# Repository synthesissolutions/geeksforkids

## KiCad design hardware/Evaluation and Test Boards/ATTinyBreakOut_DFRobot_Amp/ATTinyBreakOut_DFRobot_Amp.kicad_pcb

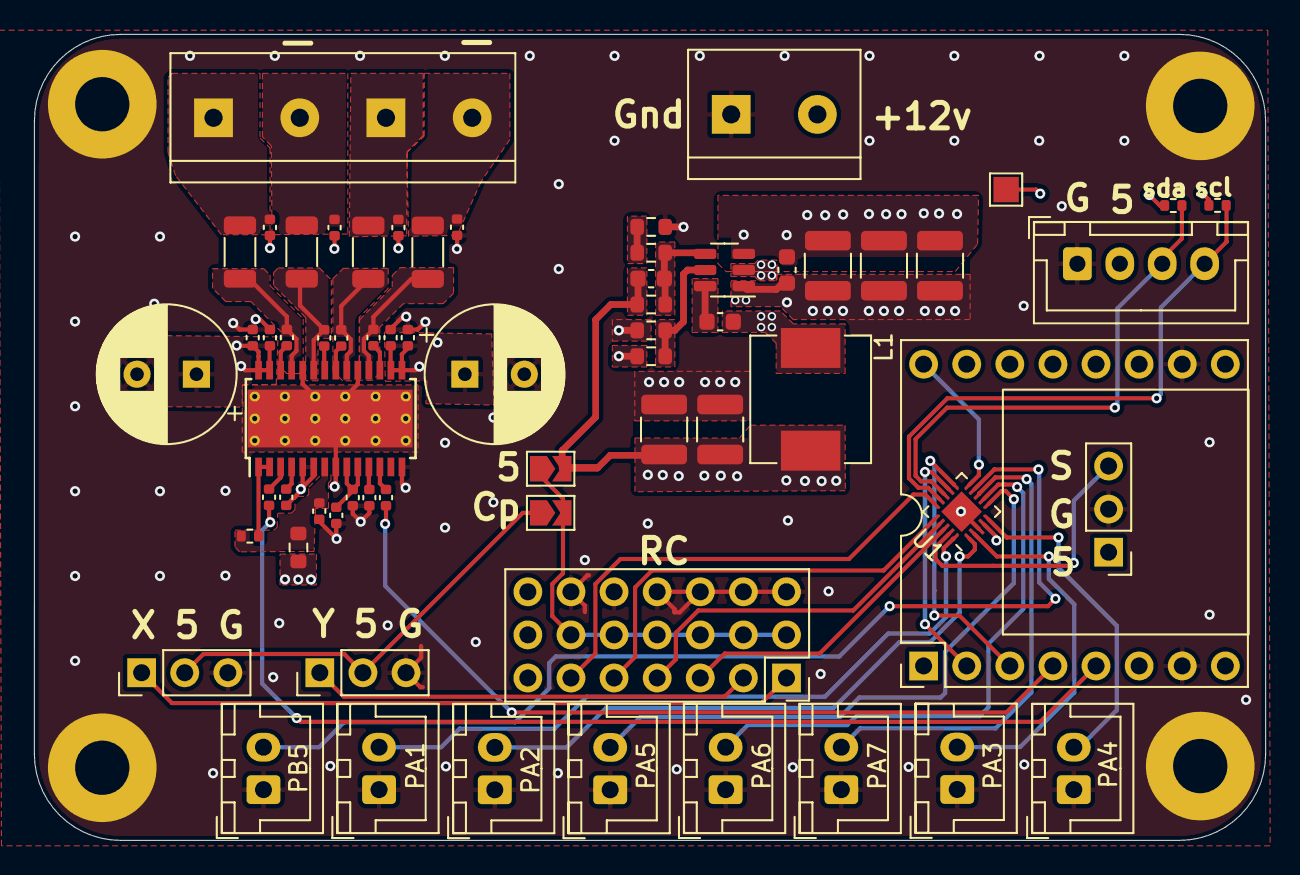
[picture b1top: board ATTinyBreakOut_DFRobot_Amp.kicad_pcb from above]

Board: 4 copper layers, 72.6 x 47.5 mm, 71 parts (0 on the bottom side), 51 nets.

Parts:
C1, C5: 100uF; CP_Radial_D8.0mm_P3.50mm
C2, C6: 100nF; C_0402_1005Metric
C3, C7, C9, C10, C24, C25: 1nF; C_0402_1005Metric
C4, C14, C15: 1uF; C_0402_1005Metric
C8, C13, C26, C29: 0.22uF; C_0402_1005Metric
C11, C12, C27, C28: 0.68uF; C_0402_1005Metric
C16, C17, C18: 10µF; C_1210_3225Metric
C19, C20: 0.1µF; C_0603_1608Metric
C21: 150pF; C_0603_1608Metric
C22, C23: 47µF; C_1210_3225Metric
FB1, FB2, FB3, FB4: 120Ohm@100MHz; L_1206_3216Metric
H1, H2, H3, H4: MountingHole; MountingHole_3.2mm_M3_Pad
J1: Right Out; TerminalBlock_bornier-2_P5.08mm
J2: Steering; PinHeader_1x03_P2.54mm_Vertical
J3: Throttle; PinHeader_1x03_P2.54mm_Vertical
J4: Main Power; TerminalBlock_bornier-2_P5.08mm
J5: RC Signal; PinSocket_1x07_P2.54mm_Vertical
J6: ATT Prog; PinHeader_1x03_P2.54mm_Vertical
J7: RC Power; PinSocket_2x07_P2.54mm_Vertical
J8: I2C; JST_XH_B4B-XH-A_1x04_P2.50mm_Vertical
J9: PA3; JST_XH_B2B-XH-A_1x02_P2.50mm_Vertical
J10: DFRobot_Mini; DFRobotMini_2x08_P2.54mm_Vertical
J11: PA7; JST_XH_B2B-XH-A_1x02_P2.50mm_Vertical
J12: PA5; JST_XH_B2B-XH-A_1x02_P2.50mm_Vertical
J13: PA1; JST_XH_B2B-XH-A_1x02_P2.50mm_Vertical
J14: PB5; JST_XH_B2B-XH-A_1x02_P2.50mm_Vertical
J15: PA2; JST_XH_B2B-XH-A_1x02_P2.50mm_Vertical
J16: Left Out; TerminalBlock_bornier-2_P5.08mm
J17: PA6; JST_XH_B2B-XH-A_1x02_P2.50mm_Vertical
J18: PA4; JST_XH_B2B-XH-A_1x02_P2.50mm_Vertical
JP1: Car Power; SolderJumper-2_P1.3mm_Open_TrianglePad1.0x1.5mm
JP2: 5v; SolderJumper-2_P1.3mm_Open_TrianglePad1.0x1.5mm
L1: 10µH; L_Sunlord_MWSA0603S
R1: 10R; R_0603_1608Metric
R2, R4: 4.7k; R_0402_1005Metric
R3: 100k; R_0402_1005Metric
R11: 511kΩ 1%; R_0603_1608Metric
R12: 105kΩ 1%; R_0603_1608Metric
R13: 100kΩ 1%; R_0603_1608Metric
R14: 13.3kΩ 1%; R_0603_1608Metric
R15: 240Ω 1%; R_0603_1608Metric
TP1: 5V; TestPoint_Pad_1.5x1.5mm
U1: ATtiny1616-M; VQFN-20-1EP_3x3mm_P0.4mm_EP1.7x1.7mm
U3: TPA3110D2; HTSSOP-28-1EP_4.4x9.7mm_P0.65mm_EP3.4x9.5mm_Mask2.4x6.17mm_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
U4: TPS54302; SOT-23-6

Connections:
+5V: C21.1, C22.1, C23.1, J6.1, J8.2, J10.1, JP2.2 (B), L1.2, R2.1, R4.1, R13.1, TP1.1, U1.4 (VCC)
+12V: C1.1, C2.1, C3.1, C5.1, C6.1, C7.1, C16.1, C17.1, C18.1, C19.1, J4.2, R1.1, R11.1, U3.15 (PVCCR), U3.16 (PVCCR), U3.27 (PVCCL), U3.28 (PVCCL), U4.3 (VIN)
+12VA: C4.1, R1.2, R3.1, U3.7 (AVCC)
/Audio_Module/AUDIO_IN_1_NL: C27.1, U3.4 (LINN)
/Audio_Module/AUDIO_IN_1_NR: C12.1, U3.11 (RINN)
/Audio_Module/AUDIO_IN_1_PL: C28.2, U3.3 (LINP)
/Audio_Module/AUDIO_IN_1_PR: C11.2, U3.12 (RINP)
/Audio_Module/AUDIO_OUT_FILT_NL: C10.2, FB2.2, J16.2
/Audio_Module/AUDIO_OUT_FILT_NR: C25.2, FB4.2, J1.2
/Audio_Module/AUDIO_OUT_FILT_PL: C9.1, FB1.2, J16.1
/Audio_Module/AUDIO_OUT_FILT_PR: C24.1, FB3.2, J1.1
/Audio_Module/GVDD: C14.1, C15.1, U3.9 (GVDD), U3.10 (PLIMIT)
/Audio_Module/~SD_2: R3.2, U3.1 (~SD), U3.2 (~FAULT)
/Buck_Converter/BOOT: C20.1, U4.6 (BOOT)
/Buck_Converter/EN: R11.2, R12.1, U4.5 (EN)
/Buck_Converter/FB: C21.2, R13.2, R14.1, U4.4 (FB)
/Buck_Converter/SW: C20.2, L1.1, U4.2 (SW)
ATT_Prog: J6.3, U1.19 (~RESET/PA0)
AUDIO_IN_PL: C28.1, J10.9
AUDIO_IN_PR: C11.1, J10.7
Car_Power: J7.1, J7.3, J7.5, J7.7, J7.9, J7.11, JP1.2 (B), JP2.1 (A)
DFR_Busy: J10.2, U1.10 (PB4)
DFR_Rx: J10.3, U1.12 (PB2)
DFR_Tx: J10.5, U1.11 (PB3)
GND: C1.2, C2.2, C3.2, C4.2, C5.2, C6.2, C7.2, C9.2, C10.1, C12.2, C14.2, C15.2, C16.2, C17.2, C18.2, C19.2, C22.2, C23.2, C24.2, C25.1, C27.2, H1.1, H2.1, H3.1, H4.1, J2.3, J3.3, J4.1, J6.2, J7.2, J7.4, J7.6, J7.8, J7.10, J7.12, J8.1, J9.1, J10.13, J10.14, J11.1, J12.1, J13.1, J14.1, J15.1, J17.1, J18.1, R12.2, R15.2, U1.3 (GND), U1.21 (GND), U3.5 (GAIN0), U3.6 (GAIN1), U3.8 (AGND), U3.14 (PBTL), U3.19 (PGND), U3.24 (PGND), U3.29 (GND), U4.1 (GND)
I2C_SCL: J8.4, R2.2, U1.14 (PB0)
I2C_SDA: J8.3, R4.2, U1.13 (PB1)
unnamed: J2.2, J3.2, JP1.1 (A)
unnamed: R14.2, R15.1
unnamed: C26.2, U3.22 (BSNL)
unnamed: C29.2, U3.21 (BSNR)
unnamed: C8.2, U3.26 (BSPL)
unnamed: C13.2, U3.17 (BSPR)
unnamed: C26.1, FB2.1, U3.23 (OUTNL)
unnamed: C29.1, FB3.1, U3.20 (OUTNR)
unnamed: C8.1, FB1.1, U3.25 (OUTPL)
unnamed: C13.1, FB4.1, U3.18 (OUTPR)
PA1: J13.2, U1.20 (PA1)
PA2: J15.2, U1.1 (PA2)
PA3: J9.2, U1.2 (PA3)
PA4: J18.2, U1.5 (PA4)
PA5: J12.2, U1.6 (PA5)
PA6: J17.2, U1.7 (PA6)
PA7: J11.2, U1.8 (PA7)
PB5: J14.2, U1.9 (PB5)
RC_3: J5.3, U1.18 (PC3)
RC_4: J5.4, U1.17 (PC2)
RC_5: J5.5, U1.16 (PC1)
RC_6: J5.6, U1.15 (PC0)
RC_X: J2.1, J5.1
RC_Y: J3.1, J5.2

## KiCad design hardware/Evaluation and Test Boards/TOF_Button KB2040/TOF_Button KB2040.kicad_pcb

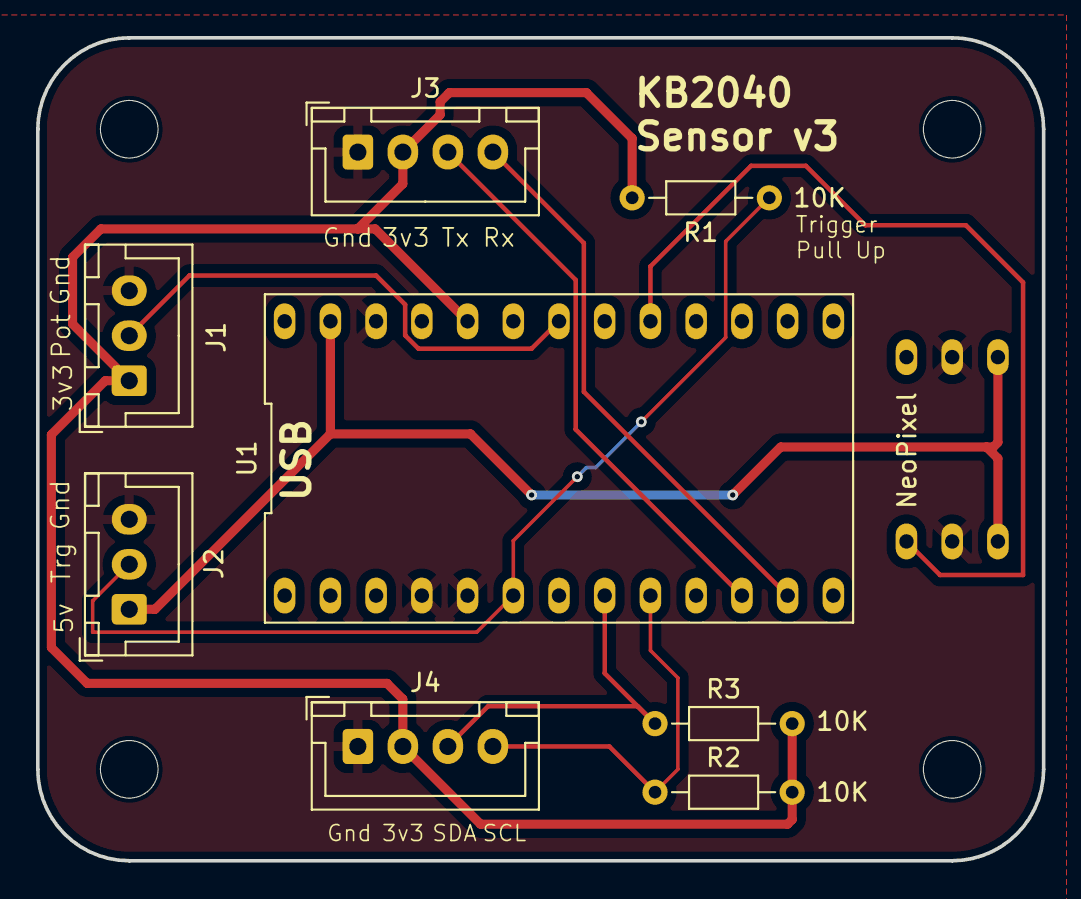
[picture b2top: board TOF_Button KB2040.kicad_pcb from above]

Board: 2 copper layers, 55.9 x 45.7 mm, 13 parts (1 on the bottom side), 10 nets.

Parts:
H1, H2, H3, H4: MountingHole; MountingHole_3.2mm_M3
J1: Potentiometer; JST_XH_B3B-XH-A_1x03_P2.50mm_Vertical
J2: Power In Signal Out; JST_XH_B3B-XH-A_1x03_P2.50mm_Vertical
J3, J4: Conn_01x04_Pin; JST_XH_B4B-XH-A_1x04_P2.50mm_Vertical
R1, R2, R3: 10K; R_Axial_DIN0204_L3.6mm_D1.6mm_P7.62mm_Horizontal
U1: Adafruit KB2040
U2: NeoPixel_Breadboard

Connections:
+3V3: J1.1, J3.2, J4.2, R1.2, R2.2, R3.2, U1.22 (3v3)
+5V: J2.1, U1.25 (RAW), U2.1 (5v), U2.6 (5v)
Distance_Pot: J1.2, U1.20 (A2)
GND: J1.3, J2.3, J3.1, J4.1, U1.4 (GND), U1.5 (GND), U1.24 (GND), U2.2 (Gnd), U2.5 (Gnd)
NeoPixel_Data: U1.18 (A0), U2.3 (DataIn)
RX: J3.4, U1.12 (D8)
SCL: J4.4, R2.1, U1.9 (D5)
SDA: J4.3, R3.1, U1.8 (D4)
TX: J3.3, U1.11 (D7)
Trigger_Out: J2.2, R1.1, U1.6 (D2)

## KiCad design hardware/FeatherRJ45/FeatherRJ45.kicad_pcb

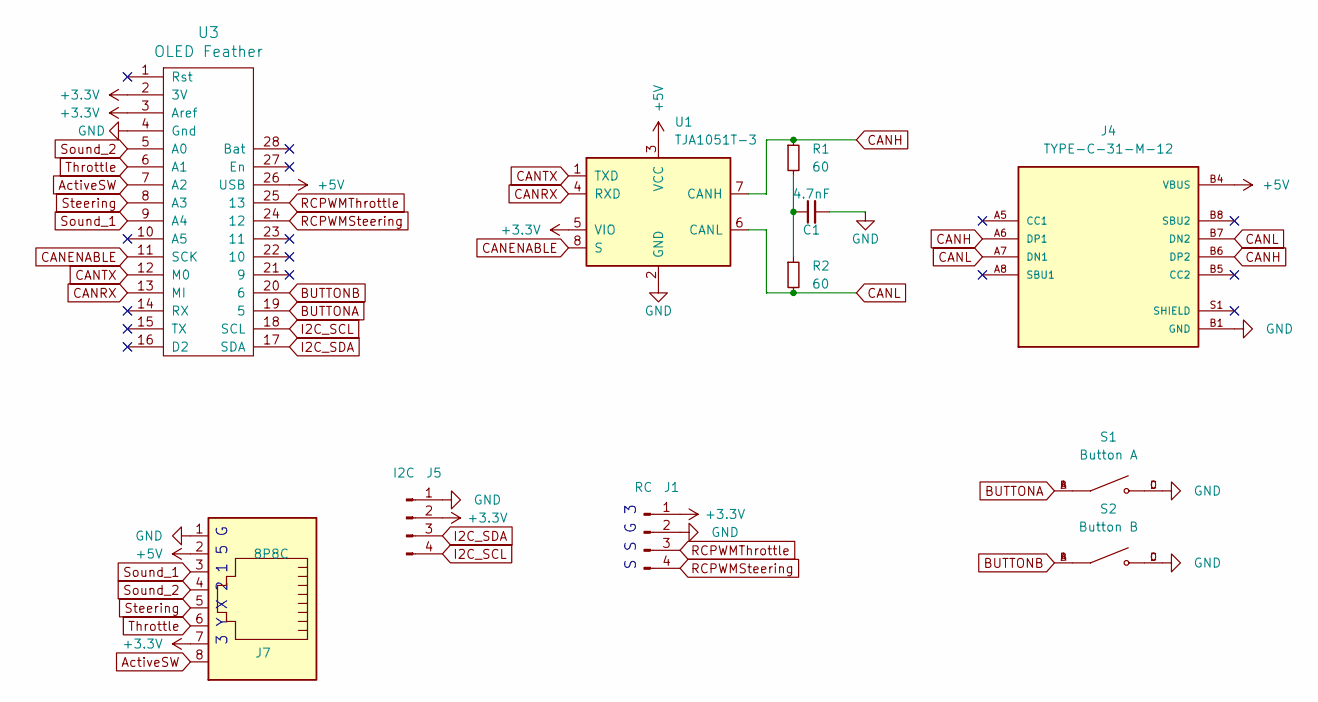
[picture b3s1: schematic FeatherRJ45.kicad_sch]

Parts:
C1: 4.7nF; C_0402_1005Metric; MPN C1538
J1: RC; JST_XH_B4B-XH-A_1x04_P2.50mm_Vertical
J4: TYPE-C-31-M-12; MPN C165948
J5: I2C; JST_SH_BM04B-SRSS-TB_1x04-1MP_P1.00mm_Vertical; MPN C145961
J7: 8P8C; RJ45_x08_Tab_Up
R1, R2: 60; R_0402_1005Metric; MPN C137954
S1: Button A; SW_TS-1187A-B-A-B; MPN C318884
S2: Button B; SW_TS-1187A-B-A-B; MPN C318884
U1: TJA1051T-3; SOIC-8_3.9x4.9mm_P1.27mm; MPN C5342108
U3: OLED Feather; Feather_nRF52840

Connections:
+3V3: J1.1, J5.2, J7.7, U1.5 (VIO), U3.2 (3V), U3.3 (Aref)
+5V: J4.A4 (VBUS), J4.A9 (VBUS), J4.B4 (VBUS), J4.B9 (VBUS), J7.2, U1.3 (VCC), U3.26 (USB)
ActiveSW: J7.8, U3.7 (A2)
BUTTONA: S1.A, S1.B, U3.19 (5)
BUTTONB: S2.A, S2.B, U3.20 (6)
CANENABLE: U1.8 (S), U3.11 (SCK)
CANH: J4.A6 (DP1), J4.B6 (DP2), R1.1, U1.7 (CANH)
CANL: J4.A7 (DN1), J4.B7 (DN2), R2.2, U1.6 (CANL)
CANRX: U1.4 (RXD), U3.13 (MI)
CANTX: U1.1 (TXD), U3.12 (M0)
GND: C1.2, J1.2, J4.A1 (GND), J4.A12 (GND), J4.B1 (GND), J4.B12 (GND), J5.1, J7.1, S1.C, S1.D, S2.C, S2.D, U1.2 (GND), U3.4 (Gnd)
I2C_SCL: J5.4, U3.18 (SCL)
I2C_SDA: J5.3, U3.17 (SDA)
unnamed: C1.1, R1.2, R2.1
RCPWMSteering: J1.4, U3.24 (12)
RCPWMThrottle: J1.3, U3.25 (13)
Sound_1: J7.3, U3.9 (A4)
Sound_2: J7.4, U3.5 (A0)
Steering: J7.5, U3.8 (A3)
Throttle: J7.6, U3.6 (A1)

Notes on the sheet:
S S G 3
3 Y X 2 1 5 G

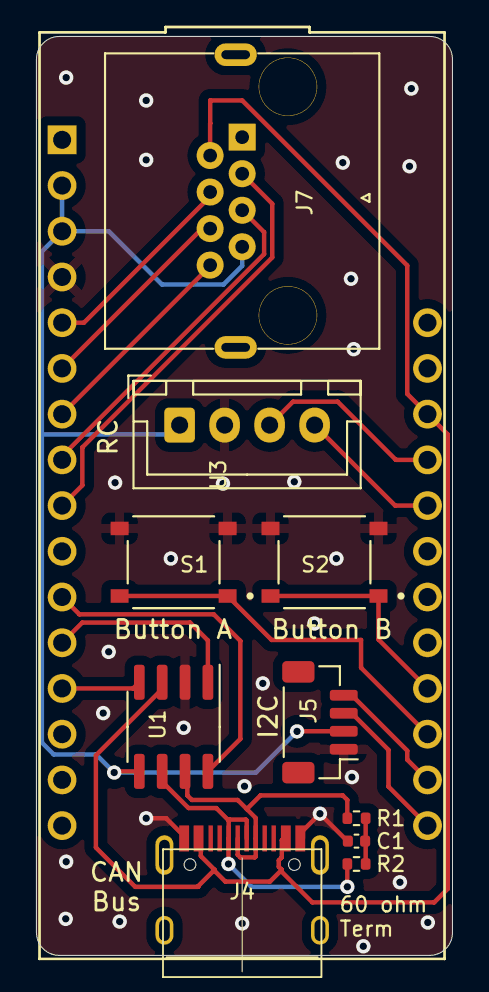
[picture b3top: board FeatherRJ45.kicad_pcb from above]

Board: 2 copper layers, 23.1 x 51.1 mm, 11 parts (0 on the bottom side), 20 nets.

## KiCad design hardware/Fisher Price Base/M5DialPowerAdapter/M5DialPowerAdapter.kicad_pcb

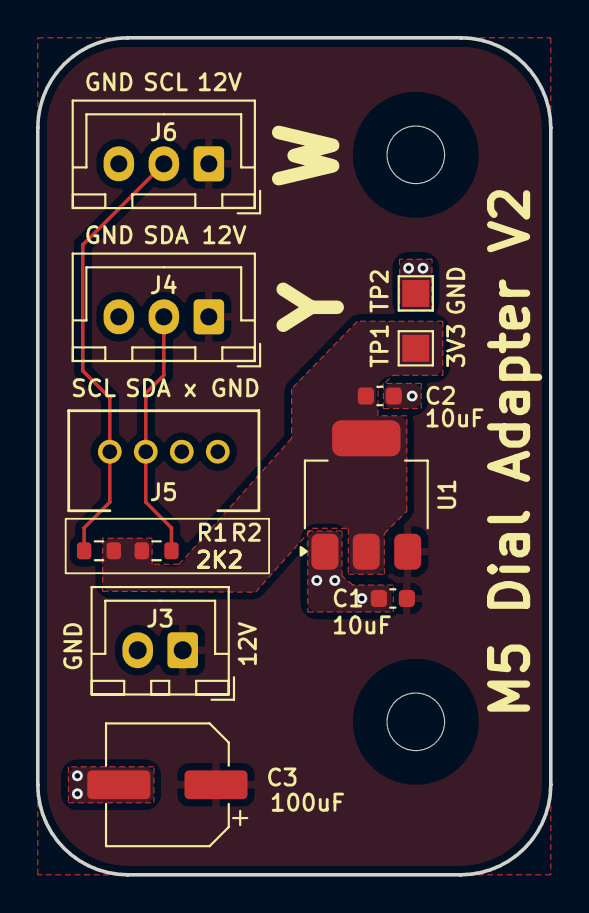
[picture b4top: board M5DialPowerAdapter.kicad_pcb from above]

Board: 2 copper layers, 28.5 x 46.5 mm, 14 parts (0 on the bottom side), 5 nets.

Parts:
C1, C2: 10uF; C_0603_1608Metric
C3: 100uF; CP_Elec_6.3x7.7
H1, H2: MountingHole_3.2mm_M3
J3: M5Dial Power; JST_XH_B2B-XH-A_1x02_P2.50mm_Vertical
J4: JST XH SCA; JST_XH_B3B-XH-A_1x03_P2.50mm_Vertical
J5: Grove I2C; CONN_110990030_SEE
J6: JST XH SCL; JST_XH_B3B-XH-A_1x03_P2.50mm_Vertical
R1, R2: 2K2; R_0603_1608Metric
TP1: 3V3; TestPoint_Pad_1.5x1.5mm
TP2: GND; TestPoint_Pad_1.5x1.5mm
U1: AMS1117-3.3; SOT-223-3_TabPin2

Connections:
+3V3: C2.1, R1.2, R2.2, TP1.1, U1.2 (VO)
+12V: C1.1, C3.1, J3.1, J4.1, J6.1, U1.3 (VI)
GND: C1.2, C2.2, C3.2, J3.2, J4.3, J5.4, J6.3, TP2.1, U1.1 (GND)
SCL: J5.1, J6.2, R1.1
SDA: J4.2, J5.2, R2.1

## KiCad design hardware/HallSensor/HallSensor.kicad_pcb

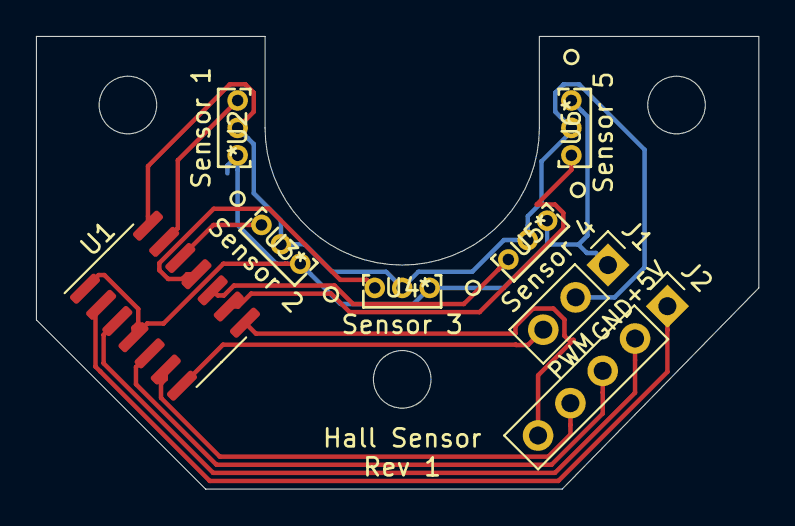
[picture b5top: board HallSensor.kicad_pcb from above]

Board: 2 copper layers, 40.1 x 25.1 mm, 8 parts (0 on the bottom side), 13 nets.

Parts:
J1: Power_Signal; PinHeader_1x03_P2.54mm_Vertical
J2: Breakout; PinHeader_1x05_P2.54mm_Vertical
U1: ATtiny841-SSU; SOIC-14_3.9x8.7mm_P1.27mm
U2: Sensor 1; SS49E
U3: Sensor 2; SS49E
U4: Sensor 3; SS49E
U5: Sensor 4; SS49E
U6: Sensor 5; SS49E

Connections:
+5V: J1.1, U1.1, U1.4, U2.1, U3.1, U4.1, U5.1, U6.1
GND: J1.2, U1.14, U2.2, U3.2, U4.2, U5.2, U6.2
unnamed: J1.3, U1.7
unnamed: J2.1, U1.2
unnamed: J2.2, U1.3
unnamed: J2.3, U1.5
unnamed: J2.4, U1.6
unnamed: J2.5, U1.8
unnamed: U1.9, U6.3
unnamed: U1.10, U5.3
unnamed: U1.11, U4.3
unnamed: U1.12, U3.3
unnamed: U1.13, U2.3

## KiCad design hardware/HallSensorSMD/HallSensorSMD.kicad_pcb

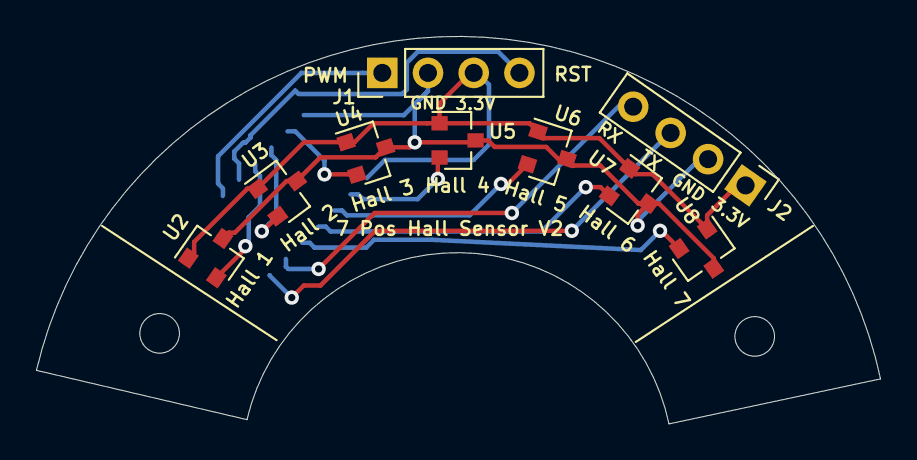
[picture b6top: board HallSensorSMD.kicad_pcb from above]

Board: 2 copper layers, 46.9 x 21.5 mm, 10 parts (1 on the bottom side), 13 nets.

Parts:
J1: Power/Signal; PinHeader_1x04_P2.54mm_Vertical
J2: RX/TX; PinHeader_1x04_P2.54mm_Vertical
U1: ATtiny814; SOIC-14_3.9x8.7mm_P1.27mm
U2: Hall 1; SOT-23
U3: Hall 2; SOT-23
U4: Hall 3; SOT-23
U5: Hall 4; SOT-23
U6: Hall 5; SOT-23
U7: Hall 6; SOT-23
U8: Hall 7; SOT-23

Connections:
+3V3: J1.3, J2.1, U1.1, U2.1, U3.1, U4.1, U5.1, U6.1, U7.1, U8.1
GND: J1.2, J2.2, U1.14, U2.3, U3.3, U4.3, U5.3, U6.3, U7.3, U8.3
unnamed: J1.1, U1.9
unnamed: J1.4, U1.10
unnamed: J2.3, U1.7
unnamed: J2.4, U1.6
unnamed: U1.2, U5.2
unnamed: U1.3, U6.2
unnamed: U1.4, U7.2
unnamed: U1.5, U8.2
unnamed: U1.11, U2.2
unnamed: U1.12, U3.2
unnamed: U1.13, U4.2

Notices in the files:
parts and their libraries:
Copyright 2016 Accelerated Designs. All rights reserved.
